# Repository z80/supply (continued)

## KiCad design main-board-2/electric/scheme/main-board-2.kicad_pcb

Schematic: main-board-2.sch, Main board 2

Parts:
C1, C6: 54u
C2, C4, C5, C14: 4u7
C3, C9, C10, C11, C12, C13, C15, C16: 100n
C7, C8: 18p
D1, D2: LED
D3, D4, D5, D6, D7, D8, D9, D10: 1n5819
K1: power-switch
K2: usb-power-switch
P1: batt
P3: trigger-btn
P4: CONN_3X2
P7: bootloader
P8: cross board conn
P9, P10: rst
P11: screw-1
P13: screw-2
P14: gpio-big
P15: gpio-small
P16: moto-1
P17: moto-2
Q1, Q3, Q4, Q9, Q10: IRLML2244
Q2, Q5, Q6, Q7, Q8: BC847
Q11: sot223
Q12: bc857
Q13: irlml2244
R1, R3, R6, R10, R22, R23, R26, R27: 1k
R2, R7, R9, R11, R12, R14, R18, R19, R20, R21, R24, R25, R28, R29, R30, R31: 30k
R4: 3k3
R5: 5k1
R8: 3k
R13: 50
R15, R16, R17: 10k
R32, R33: 22
R34: 1k5
R35: 100k
R36, R37, R38, R39: 0.1
R40, R42, R48, R49: 30k
R41, R43, R44, R45: 1k
R46, R47: 3
U1, U3: MY_LM317EMP; SOT-223
U2, U4: MY_LM317T; TO-220
U5: LM293
U6: L298
U7: MINI-USB-B
W1: sc-rpi-5v
W2: sc-addon-5v
W3: sc-addon-3.3
W4, W5, W10: TEST
W6: sc-sense-2
W7: sc-sense-1
W8: sc-moto-2
W9: sc-moto-1
X1: 8MHz
stm1: STM32F102C8T6

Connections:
/+5V: K1.2 (PM), K2.1, Q1.S, Q3.S, Q10.S, R9.2, R20.2, R30.1, W1.1, W2.1, W4.1
/addon-5V: P8.8, P8.9, Q3.D, W2.2
/addon-pwr-en: R22.1, R23.1, R24.2, stm1.26 (PB13/SPI2_SCK/USART3_CTS)
/addon-trigger: R17.2, stm1.19 (PB1/ADC_IN9/TIM3_CH4)
/addon-vdd: P8.6, P8.7, Q4.D, R15.1, R16.1, W3.2
/batt+: C1.1, C2.1, D3.2 (K), D5.2 (K), D7.2 (K), D9.2 (K), K1.3, P1.1, P8.10, P8.11, Q9.S, Q11.S, Q13.D, R28.1, R49.2, U1.3, U2.3, U3.3, U4.3, W5.1, W10.2
/cur-sense-1: R37.1, R39.1, U5.6 (_), U6.1 (current-sensing-A), W7.1
/cur-sense-2: R36.1, R38.1, U5.2 (_), U6.15 (current-sensing-B), W6.1
/d+: R33.1, stm1.33 (PA12/USART1_RTS/USBDP)
/d-: R32.1, stm1.32 (PA11/USART1_CTS/USBDM)
/gpio-1: P14.5, stm1.25 (PB12/SPI2_NSS/I2C2_SMBA/USART3_CTS)
/gpio-2: P14.11, stm1.18 (PB0/ADC_IN8/TIM3_CH3)
/gpio-3: P14.17, stm1.15 (PA5/SPI1_SCK/ADC_IN5)
/gpio-4: P14.23, stm1.13 (PA3/USART2_RX/ADC_IN3/TIM2_CH4)
/gpio-5: P14.6, stm1.27 (PB14/SPI2_MISO/USART3_RTS)
/gpio-6: P14.12, stm1.17 (PA7/SPI1_MOSI/ADC_IN7/TIM3_CH2)
/gpio-7: P14.18, stm1.16 (PA6/SPI1_MISO/ADC_IN6/TIM3_CH1)
/gpio-8: P14.24, stm1.14 (PA4/SPI1_NSS/ADC_IN4/USART2_CK)
/gpio-9: P15.1, stm1.12 (PA2/USART2_TX/ADC_IN2/TIM2_CH3)
/in-moto1: U6.5 (input-1), stm1.11 (PA1/USART2_RTS/ADC_IN1/TIM2_CH2)
/in-moto2: U6.7 (input-2), stm1.10 (PA0/WKUP/USART2_CTS/ADC_IN0/TIM2_CH1_ETR)
/in-moto3: U6.10 (input-3), stm1.3 (PC14/OSC32_IN)
/in-moto4: U6.12 (input-4), stm1.4 (PC15/OSC32_OUT)
/led1: R1.1, stm1.46 (PB9/TIM4_CH4^I2C1_SDA)
/led2: R3.1, stm1.45 (PB8/TIM4_CH3^I2C1_SCL)
/moto-en: R25.2, R26.1, R27.1, R44.1, R45.1, W8.1, W9.1, stm1.2 (PC13/TAMPER-RTC)
/moto-en-1: R45.2, U5.7, U6.6 (enable-A), W9.2
/moto-en-2: R44.2, U5.1, U6.11 (enable-B), W8.2
/out1: D9.1 (A), D10.2 (K), P16.1, U6.2 (output-1)
/out2: D7.1 (A), D8.2 (K), P16.2 (PM), U6.3 (output-2)
/out3: D5.1 (A), D6.2 (K), P17.1, U6.13 (output-3)
/out4: D3.1 (A), D4.2 (K), P17.2 (PM), U6.14 (output-4)
/pwrVs: C15.1, P14.3, P14.4, P14.9, P14.10, P14.15, P14.16, P14.21, P14.22, Q9.D, Q11.D, U6.4 (power_Vs), W5.2
/rpi-pwr-en: R10.1, R11.2, stm1.41 (PB5/I2C1_SMBA^TIM3_CH2/SPI1_MOSI)
/rx: P15.3, stm1.31 (PA10/USART1_RX)
/scl-int: P8.3, R16.2, stm1.21 (PB10/I2C2_SCL/USART3_TX^TIM2_CH3)
/scl-rpi: P4.5, stm1.42 (PB6/I2C1_SCL/TIM4_CH1^USART1_TX)
/sda-int: P8.2, R15.2, stm1.22 (PB11/I2C2_SDA/USART3_RX^TIM2_CH4)
/sda-rpi: P4.3, stm1.43 (PB7/I2C1_SDA/TIM4_CH3^USART1_RX)
/swd-clk: P15.4, stm1.37 (JTCK/SWCLK^PA14)
/swd-io: P15.6, stm1.34 (JTMS/SWDIO^PA13)
/trigger-button: P3.1, R2.1, stm1.29 (PA8/USART1_CK/MCO)
/tx: P15.5, stm1.30 (PA9/USART1_TX)
/usb-connected: R34.2, stm1.28 (PB15/SPI2_MOSI)
/usb-power: K2.2 (PM), U7.1 (VBus)
GND: C1.2, C2.2, C3.2, C4.2, C5.2, C6.2, C7.1, C8.1, C9.1, C10.2, C11.2, C12.2, C13.2, C14.2, C15.2, C16.2, D1.2 (K), D2.2 (K), D4.1 (A), D6.1 (A), D8.1 (A), D10.1 (A), P1.2 (PM), P3.2 (PM), P4.6, P8.4, P8.5, P10.1, P14.1, P14.2, P14.7, P14.8, P14.13, P14.14, P14.19, P14.20, P15.2, Q2.1 (E), Q5.1 (E), Q6.1 (E), Q8.1 (E), R4.2, R6.2, R11.1, R12.2, R24.1, R25.1, R29.2, R35.1, R36.2, R37.2, R38.2, R39.2, R41.2, R43.2, R48.1, U5.4 (V-), U6.8 (gnd), U6.tab (gnd), U7.0 (Shell), U7.5 (Gnd), W6.2, W7.2, stm1.8 (Vssa), stm1.20 (PB2/BOOT1), stm1.23 (Vss_1), stm1.35 (Vss_2), stm1.47 (Vss_3)
unnamed: P4.2, Q1.D, W1.2
unnamed: Q8.3 (C), R30.2, R31.1
unnamed: Q10.G, R31.2
unnamed: Q4.G, R19.2
unnamed: Q12.3 (C), Q13.G, R48.2, R49.1
unnamed: Q6.3 (C), R19.1, R21.1
unnamed: Q3.G, R18.2
unnamed: Q5.3 (C), R18.1, R20.1
unnamed: Q12.2 (B), Q13.S, R46.2, R47.2
unnamed: Q7.1 (E), R29.1
unnamed: Q7.2 (B), R26.2
unnamed: Q2.2 (B), R10.2
unnamed: Q2.3 (C), R7.1, R9.1
unnamed: Q7.3 (C), Q9.G, Q11.G, R28.2
unnamed: Q1.G, R7.2
unnamed: C16.1, Q10.D, U6.9 (logic_Vss), W4.2
unnamed: R40.2, R41.1, U5.3 (+)
unnamed: R42.2, R43.1, U5.5 (+)
unnamed: R32.2, U7.2 (D-)
unnamed: R35.2, U7.4 (Id)
unnamed: C9.2, P9.1, R14.2, stm1.7 (NRST)
unnamed: P7.2 (PM), R12.1, stm1.44 (BOOT0)
unnamed: Q5.2 (B), R22.2
unnamed: Q8.2 (B), R27.2
unnamed: R13.2, stm1.6 (PD1/OSC_OUT)
unnamed: C7.2, X1.2, stm1.5 (PD0/OSC_IN)
unnamed: C8.2, R13.1, X1.1
unnamed: D2.1 (A), R3.2
unnamed: D1.1 (A), R1.2
unnamed: Q6.2 (B), R23.2
unnamed: P8.1, R17.1
unnamed: K2.3, Q12.1 (E), R46.1, R47.1, W10.1
unnamed: C4.1, C6.1, K1.1, R8.2, U3.2, U3.4, U4.2
unnamed: R6.1, R8.1, U3.1, U4.1
unnamed: R4.1, R5.1, U1.1, U2.1
unnamed: R33.2, R34.1, U7.3 (D+)
VDD: C3.1, C5.1, C10.1, C11.1, C12.1, C13.1, C14.1, P7.1, Q4.S, R2.2, R5.2, R14.1, R21.2, R40.1, R42.1, U1.2, U1.4, U2.2, U5.8 (V+), W3.1, stm1.1 (Vbat), stm1.9 (Vdda), stm1.24 (Vdd_1), stm1.36 (Vdd_2), stm1.48 (Vdd_3)

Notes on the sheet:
Chassis motors control cheme.
Indicator LEDs for debugging.
Addon power.
No I2C pullups here as there are on raspberry-pi.
Battery connection socket.
Cross board communication socket. There is one at this board. But there should be two neighbour such sockets on all other boards to be able to stack them together.
Two unconnected pins for screws. The newest Raspberry Pi contains holes for M2.5 screws.
Pin 1 is for sort of synchronization if required.
Serial bootloader activation socket.
Vo*R2/(R1+R2) = 1.25 R1=5k1, R2=3k3 => Vo=3.181818...V.
Vo*R2/(R1+R2) = 1.25 R1=10k, R2=3k => Vo=5V.
This one is optional for high voltages >20V.
RPi power.
If jumper is here USB is a voltage output.
If jumper is here USB is a voltage input.
Install either TO-220 or SO-223
Either on/off circuit or shourt-circuit wire.
Again either a couple of short circuit wires or on/off circuit.
Current limiting to 400mA when USB is used for powering the board.
This one isn't actually needed for current limiting. But when powered from battery with voltage >12V GS voltage shouldn't be greater then 12V. This resistor makes it 1/2 of batt+ value.
Current sense 0.1Ohm x 2units are 0.05Ohm. At 2Amps it would be P=2^2*0.05 = 0.2W. 0.1W per one R unit. And it is <0.125W.
Here again either short circuit wires or circuits for current limiting.
This comparator has open collector output type. So it matters only when level goes low.
Short to gnd should be done using electrolytic capacitor hole.

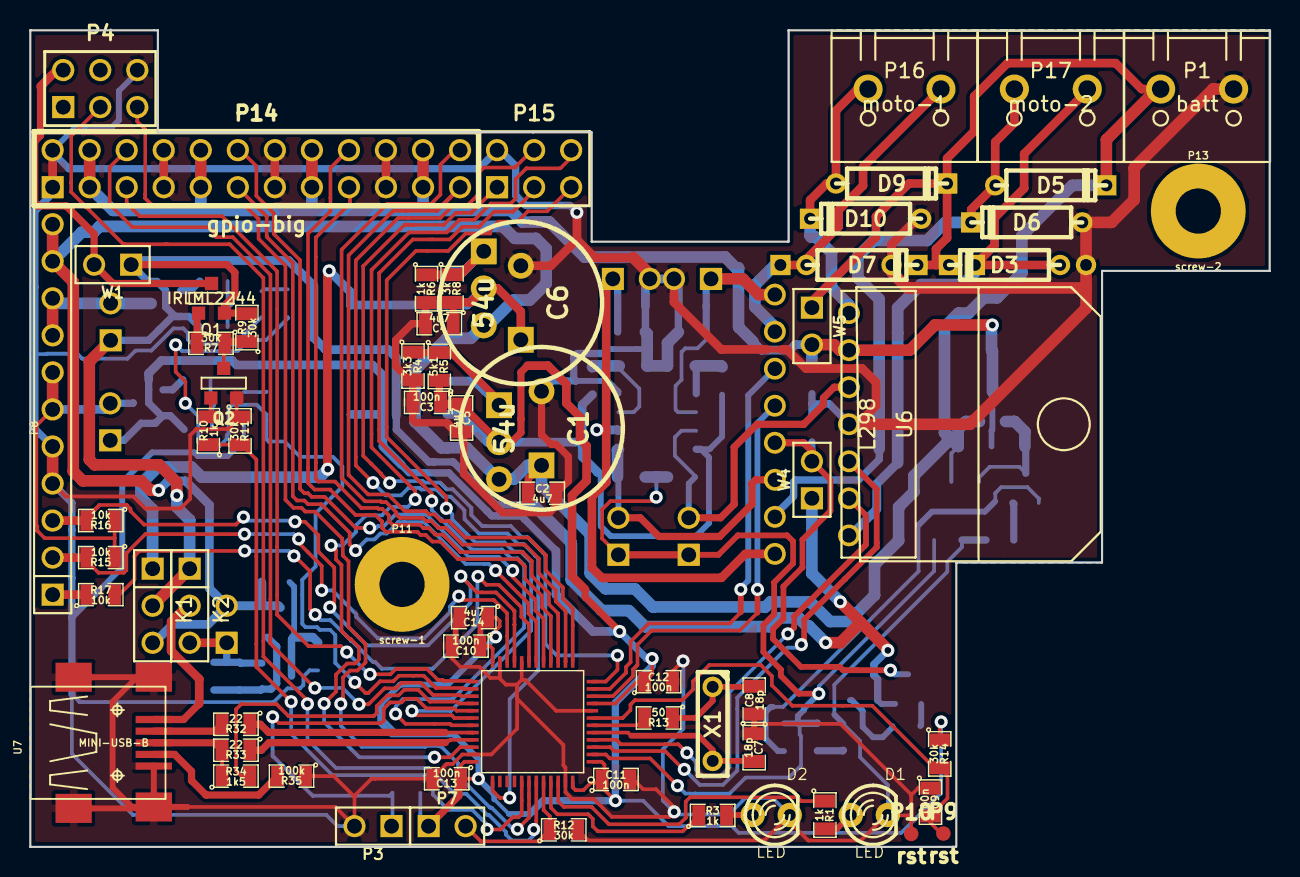
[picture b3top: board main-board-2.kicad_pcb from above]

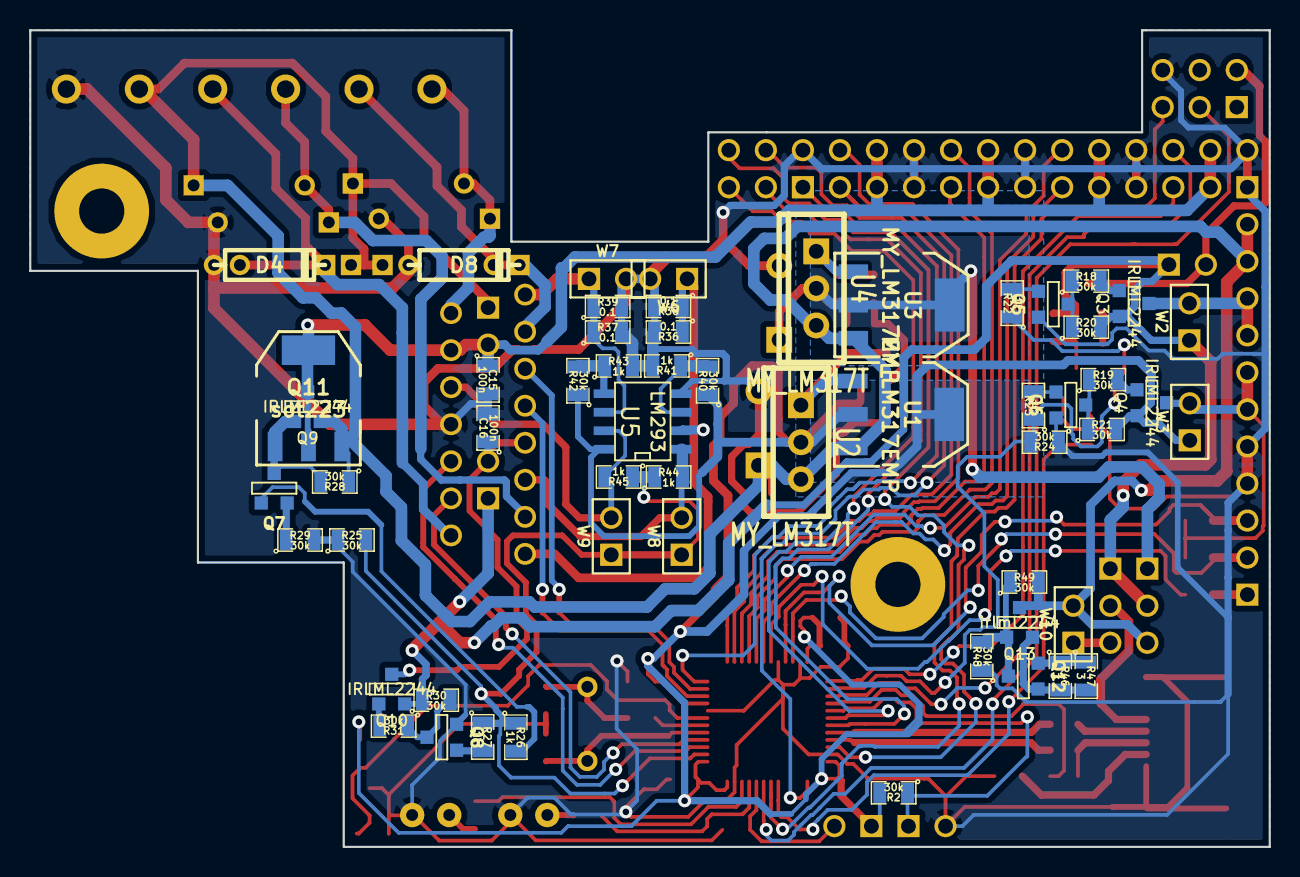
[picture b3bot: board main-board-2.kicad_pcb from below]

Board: 2 copper layers, 85.0 x 56.0 mm, 122 parts (56 on the bottom side), 83 nets.

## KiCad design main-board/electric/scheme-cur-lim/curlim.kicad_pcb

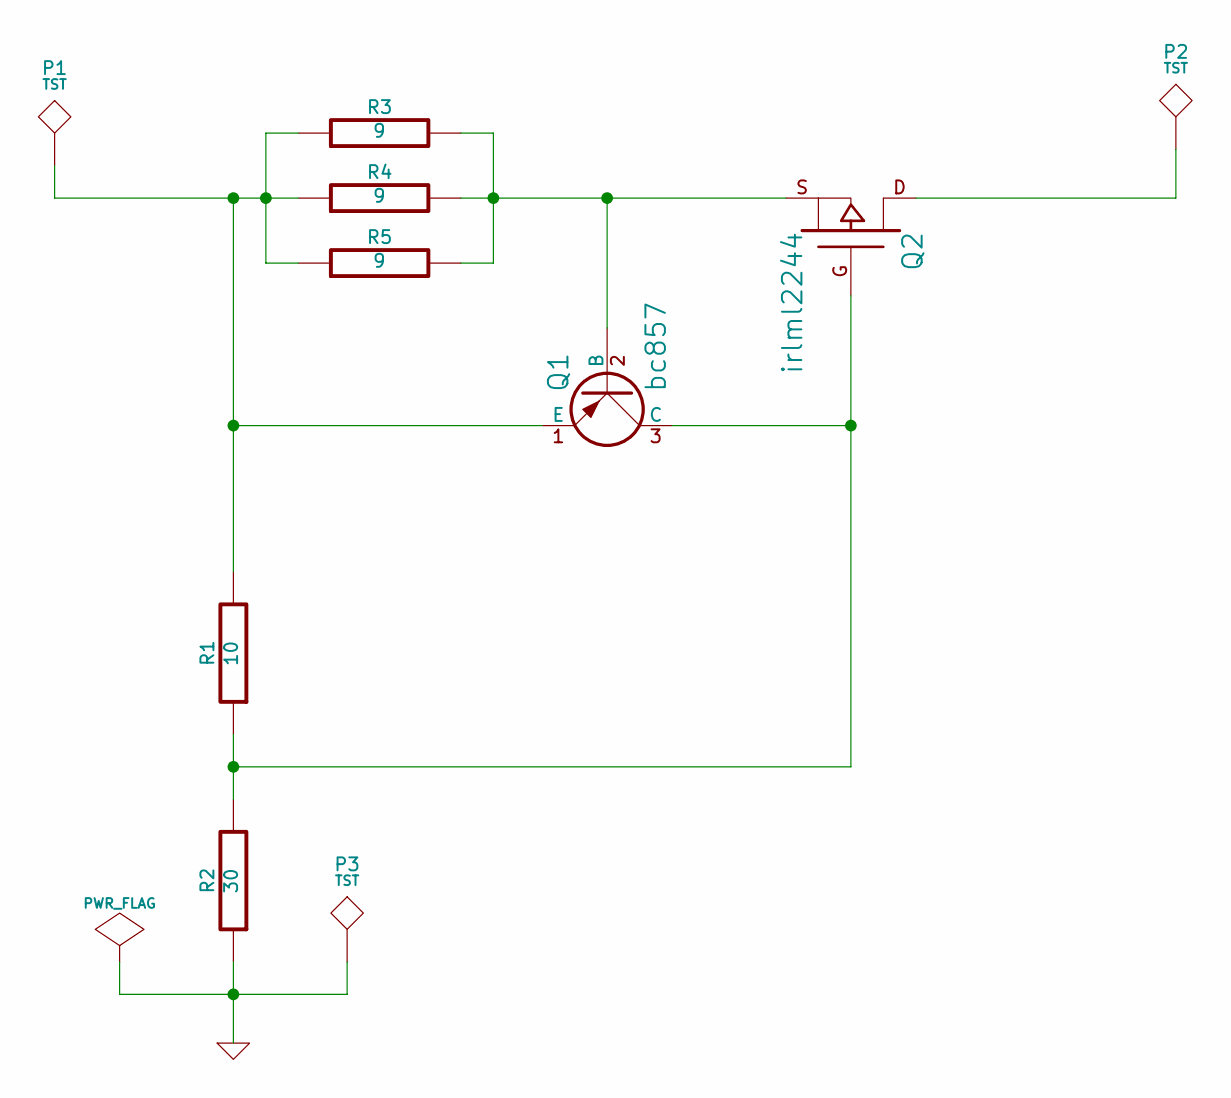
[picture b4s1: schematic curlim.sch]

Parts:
P1, P2, P3: TST
Q1: bc857
Q2: irlml2244
R1: 10
R2: 30
R3, R4, R5: 9

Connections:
GND: P3.1, R2.1
unnamed: Q1.3 (C), Q2.G, R1.1, R2.2
unnamed: P2.1, Q2.D
unnamed: Q1.2 (B), Q2.S, R3.2, R4.2, R5.2
unnamed: P1.1, Q1.1 (E), R1.2, R3.1, R4.1, R5.1

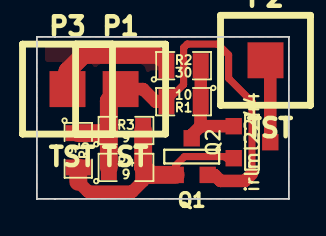
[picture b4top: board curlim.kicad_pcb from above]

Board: 2 copper layers, 14.0 x 9.0 mm, 10 parts (0 on the bottom side), 5 nets.

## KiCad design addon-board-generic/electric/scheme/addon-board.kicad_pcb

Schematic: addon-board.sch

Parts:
C1, C2, C3, C4, C5: 100n
C6: 10u
C7: 100n
C8: 10u
C9, C10: 18p
D1, D2: LED
K1, K2, K3, K4, K5, K6, K7, K8: CONN_3
P1, P2, P5, P6, P7, P8: TST
P3, P4: cross board conn
P9, P12, P13: CONN_4
P10: CONN_8
P11: CONN_10
Q1: NPN
Q2: IRLML2244
Q3, Q4: BC847
Q5, Q6: IRLML2244
R1, R2: 1k
R3, R4, R5, R6, R7, R8, R12, R13, R16, R17: 30k
R9: 1k
R10, R11: 30k
R14, R15: 500
R18, R19: 100
R20: 50
U1, U2: L293
U3: 74HC165
U4, U5: 74HC595_MY
X1: 8MHz
stm1: STM32F102C8T6

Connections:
+6V: Q5.S, Q6.S, R16.1, R17.1
/adc1: P10.1, stm1.11 (PA1/USART2_RTS/ADC_IN1/TIM2_CH2)
/adc2: P10.2, stm1.12 (PA2/USART2_TX/ADC_IN2/TIM2_CH3)
/adc3: P10.3, stm1.13 (PA3/USART2_RX/ADC_IN3/TIM2_CH4)
/adc4: P10.4, stm1.14 (PA4/SPI1_NSS/ADC_IN4/USART2_CK)
/adc5: P10.5, stm1.15 (PA5/SPI1_SCK/ADC_IN5)
/adc6: P10.6, stm1.16 (PA6/SPI1_MISO/ADC_IN6/TIM3_CH1)
/adc7: P10.7, stm1.17 (PA7/SPI1_MOSI/ADC_IN7/TIM3_CH2)
/addr0: P9.1, R8.2, stm1.27 (PB14/SPI2_MISO/USART3_RTS)
/addr1: P9.3, R7.2, stm1.28 (PB15/SPI2_MOSI)
/batt+: P3.8, P3.9, P4.8, P4.9, Q2.S
/buck-out-5v: P3.10, P3.11, P4.10, P4.11
/ds: U4.14, stm1.29 (PA8/USART1_CK/MCO)
/in0: P11.2, U3.11 (D0)
/in1: P11.3, U3.12 (D1)
/in2: P11.4, U3.13 (D2)
/in3: P11.5, U3.14 (D3)
/in4: P11.6, U3.3 (D4)
/in5: P11.7, U3.4 (D5)
/in6: P11.8, U3.5 (D6)
/in7: P11.9, U3.6 (D7)
/in-scl: U3.2 (CP), stm1.22 (PB11/I2C2_SDA/USART3_RX^TIM2_CH4)
/in-sda: U3.9 (Q7), stm1.21 (PB10/I2C2_SCL/USART3_TX^TIM2_CH3)
/iwakeup: P3.1, P4.1, R3.1
/led1: R1.1, U4.15
/led2: R2.1, U4.1
/moto1: U1.2 (in1), U4.4
/moto2: U1.9 (in2), U4.5
/moto3: U1.12 (in3), U4.6
/moto4: U1.19 (in4), U4.7
/moto5: U2.2 (in1), U5.15
/moto6: U2.9 (in2), U5.1
/moto7: U2.12 (in3), U5.2
/moto8: U2.19 (in4), U5.3
/moto-en1: R12.2, R14.1, U1.1 (en1), U1.11 (en2), U4.2
/moto-en2: R13.2, R15.1, U2.1 (en1), U2.11 (en2), U4.3
/mr: U4.10, U5.10, stm1.33 (PA12/USART1_RTS/USBDP)
/oe: U4.13, U5.13, stm1.30 (PA9/USART1_TX)
/out1: P12.3, U1.3 (out1)
/out2: P12.4, U1.8 (out2)
/out3: P12.1, U1.13 (out3)
/out4: P12.2, U1.18 (out4)
/out5: P13.3, U2.3 (out1)
/out6: P13.4, U2.8 (out2)
/out7: P13.1, U2.13 (out3)
/out8: P13.2, U2.18 (out4)
/scl-int: P3.3, P4.3, stm1.42 (PB6/I2C1_SCL/TIM4_CH1^USART1_TX)
/sda-int: P3.2, P4.2, stm1.43 (PB7/I2C1_SDA/TIM4_CH3^USART1_RX)
/servo1: K1.1, stm1.39 (JTDO^TIM2_CH2/PB3/TRACESWO/SPI1_SCKPB3)
/servo2: K2.1, stm1.40 (JNTRST^TIM3_CH1/PB4/SPI1_MISO)
/servo3: K3.1, stm1.41 (PB5/I2C1_SMBA^TIM3_CH2/SPI1_MOSI)
/servo4: K4.1, stm1.45 (PB8/TIM4_CH3^I2C1_SCL)
/servo5: K5.1, stm1.46 (PB9/TIM4_CH4^I2C1_SDA)
/servo6: K6.1, stm1.19 (PB1/ADC_IN9/TIM3_CH4)
/servo7: K7.1, stm1.18 (PB0/ADC_IN8/TIM3_CH3)
/servo8: K8.1, stm1.10 (PA0/WKUP/USART2_CTS/ADC_IN0/TIM2_CH1_ETR)
/servo-en: R9.1, U5.4
/servo-vdd+: C7.2, C8.2, K1.2 (PM), K2.2 (PM), K3.2 (PM), K4.2 (PM), K5.2 (PM), K6.2 (PM), K7.2 (PM), K8.2 (PM), Q2.D
/shcp: U4.11, U5.11, stm1.32 (PA11/USART1_CTS/USBDM)
/stcp: U4.12, U5.12, stm1.31 (PA10/USART1_RX)
/swd-clk: P5.1, stm1.37 (JTCK/SWCLK^PA14)
/swd-io: P6.1, stm1.34 (JTMS/SWDIO^PA13)
/wakeup: R3.2, stm1.3 (PC14/OSC32_IN)
/~in-load: U3.1 (~PL), stm1.26 (PB13/SPI2_SCK/USART3_CTS)
/~in-scl-en: U3.15 (~CE), stm1.25 (PB12/SPI2_NSS/I2C2_SMBA/USART3_CTS)
GND: C1.1, C2.2, C3.2, C4.2, C5.2, C6.2, C8.1, C9.1, C10.1, D1.2 (K), D2.2 (K), K1.3, K2.3, K3.3, K4.3, K5.3, K6.3, K7.3, K8.3, P3.4, P3.5, P4.4, P4.5, P7.1, P9.2, P9.4, P10.8, P11.1, P11.10, Q1.1 (E), Q3.1 (E), Q4.1 (E), R4.2, R5.2, R10.1, R11.2, R12.1, R13.1, U1.4 (gnd), U1.5 (gnd), U1.6 (gnd), U1.7 (gnd), U1.14 (gnd), U1.15 (gnd), U1.16 (gnd), U1.17 (gnd), U2.4 (gnd), U2.5 (gnd), U2.6 (gnd), U2.7 (gnd), U2.14 (gnd), U2.15 (gnd), U2.16 (gnd), U2.17 (gnd), U3.8 (GND), U4.8, U5.8, stm1.8 (Vssa), stm1.23 (Vss_1), stm1.35 (Vss_2), stm1.47 (Vss_3)
unnamed: Q3.3 (C), R16.2, R18.1
unnamed: Q5.D, U1.10 (vs), U1.20 (vss)
unnamed: Q5.G, R18.2
unnamed: Q3.2 (B), R14.2
unnamed: Q6.D, U2.10 (vs), U2.20 (vss)
unnamed: R4.1, stm1.44 (BOOT0)
unnamed: U4.9, U5.14
unnamed: C1.2, R6.2, stm1.7 (NRST)
unnamed: R5.1, stm1.20 (PB2/BOOT1)
unnamed: D2.1 (A), R2.2
unnamed: D1.1 (A), R1.2
unnamed: R20.2, stm1.6 (PD1/OSC_OUT)
unnamed: C10.2, R20.1, X1.1
unnamed: C9.2, X1.2, stm1.5 (PD0/OSC_IN)
unnamed: C7.1, Q1.3 (C), Q2.G, R11.1
unnamed: Q1.2 (B), R9.2, R10.2
unnamed: Q6.G, R19.2
unnamed: Q4.3 (C), R17.2, R19.1
unnamed: Q4.2 (B), R15.2
VDD: C2.1, C3.1, C4.1, C5.1, C6.1, P3.6, P3.7, P4.6, P4.7, R6.1, R7.1, R8.1, U3.10 (DS), U3.16 (VCC), U4.16, U5.16, stm1.1 (Vbat), stm1.9 (Vdda), stm1.24 (Vdd_1), stm1.36 (Vdd_2), stm1.48 (Vdd_3)

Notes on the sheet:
Chassis motors control cheme.
Indicator LEDs for debugging.
Programming socket is planned to be made of individual pads. And programming cable is supposed to be attached with crocodile clip.
Cross board communication socket. There is one at this board. But there should be two neighbour such sockets on all other boards to be able to stack them together.
Two unconnected pins for screws. The newest Raspberry Pi contains holes for M3 screws.
And four for screws at board corners.
Pin 1 is for waking up all other boards.

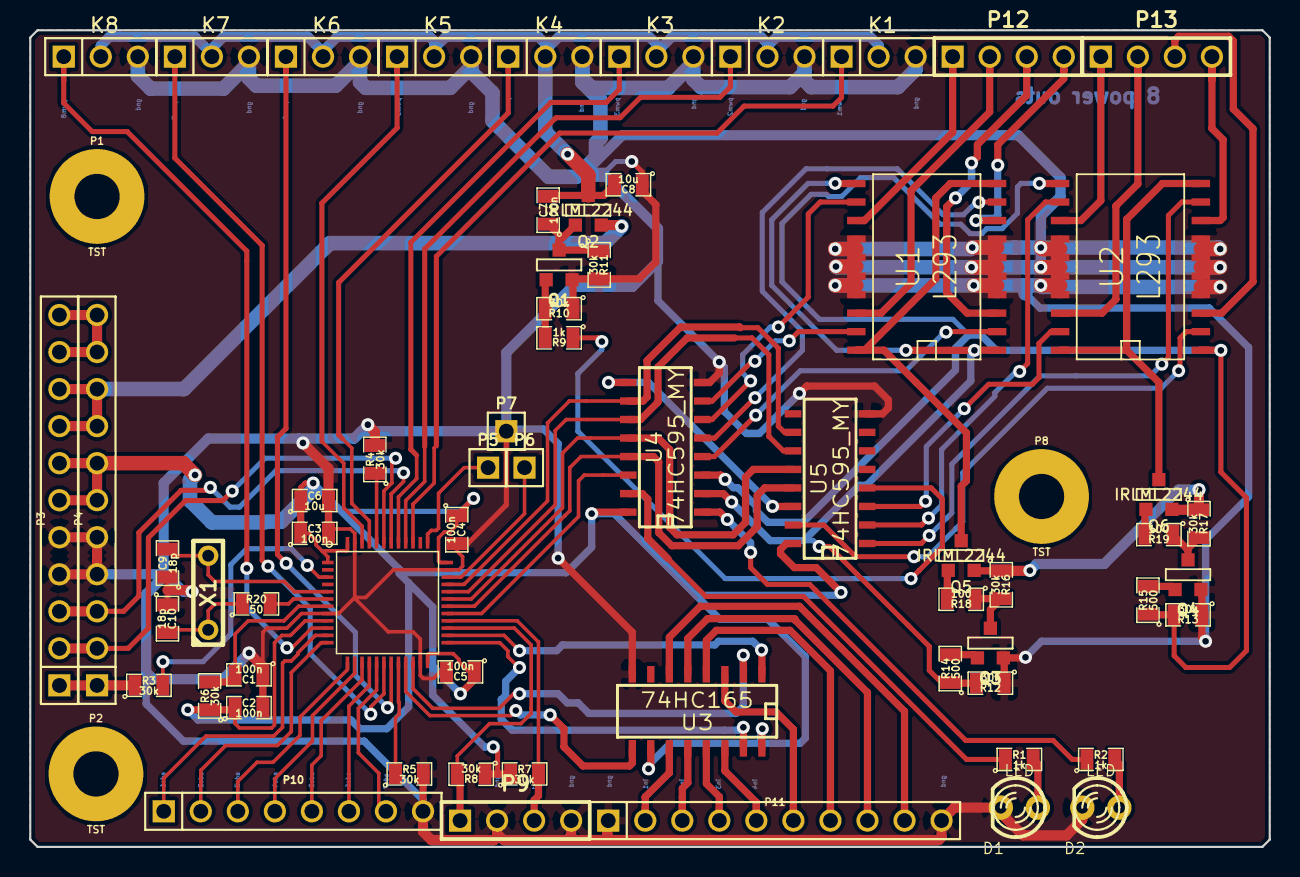
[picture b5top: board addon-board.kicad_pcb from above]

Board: 2 copper layers, 85.0 x 56.0 mm, 66 parts (0 on the bottom side), 86 nets.

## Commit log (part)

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2013-08-16 Started schematics.
2013-08-17 Board scheme development...
2013-08-19 More or less finished schema.
2013-08-20 Started placing components.
2013-08-21 Made footprints for components I didn't have footprints. And started placing components.
2013-08-23 Placing components...
2013-08-24 Placing elements.
2013-08-25 Places all but current measure circuit.
2013-08-26 Composed current measure circuit outside of the board.
2013-08-26 Routing.
2013-08-27 Routing...
2013-08-30 Routing and changing netlist to make routing more convenient.
2013-08-31 Routing is done. Added GND zones. I'm going to add text right in copper layer.
2013-08-31 Added socket labels.
2013-08-31 Added acelerometer (it's optional).
2013-08-31 .gitignore ignores _temp directory.
2013-08-31 Started extension board.
2013-09-02 Added shift registers to increase IO pins number.
2013-09-04 Placing components.
2013-09-06 Started routing.
2013-09-07 Finished routing. Holes for supports and cross board socket matches should be checked!
2013-09-07 Added more ground viases.
2013-09-09 Moved peripherial sockets closer to outer board edge.
2013-09-10 Started composing BOT for purchasing.
2013-09-10 Raplaced power mosfets with sot23 transistors because of their max current and very low resistance.
2013-09-10 For boost and buck circuits made optional sot23/sot223 transistor packages.
2013-09-11 DFU firmware. Pins adjusted for supply board.
2013-09-11 DFU software from related repository.
2013-09-11 Firmware is copied from DFU repository.
2013-09-11 Editing board.h to match current board.
2013-09-12 Splitted project into two with common code.
2013-09-13 Listed erros detected!!!
2013-09-14 Started converter implementation.
2013-09-14 Voltage converter processing.
2013-09-14 Updated ToDo list.
2013-09-15 Implemented LED and Motor control files.
2013-09-15 Fixing errors.
2013-09-16 Minimized thread switch time. Made threads cooperative.
2013-09-16 Recompiled firmware.
2013-09-17 Added one more addition.
2013-09-18 Changing pawn_pinding. Going to add RTC support.
2013-09-19 The very first in my life web design attempt.
2013-09-20 Rebuilt DFU in debug mode.
2013-09-20 Rebuilt DFU in size optimization mode.
2013-09-22 In such a way it works. But when I insert chThdSleepMilliseconds() function it hangs up at the location of the very first entry of that function.
2013-09-22 LED and Light work.
2013-09-22 Fixed ADC signal indices. Buck works.
2013-09-23 Filling Pawn binding functions.
2013-09-23 I was filling functionality.
2013-09-23 Project compiles with I2C support inserted.
2013-09-23 Filling Pawn functions.
2013-09-23 Fixed serial_ctrl.c.
2013-09-24 Adjusted TODO list.
2013-09-24 Adjusted DFU firmware. Now the idea is to start regular firmware and if trigger is pulled down invoke DFU firmware from the very end of FLASH memory.
2013-09-24 Adjusted trigger and dfu functionality. Added trigger querying function to Pawn.
2013-09-24 Rebuild under Linux.
2013-09-25 Started software. Added Pawn compiler.
2013-09-25 Preapred test for flashing Pawn scripts checking.
2013-09-25 Binary files to build in Windows.
2013-09-25 DFU library compiles under Windows.
2013-09-25 Removed unnecessary warning.
2013-09-25 .gitignore is modified to ignore unnecessary files.
2013-09-25 Fixed USB connect/disconnect pin.
2013-09-25 Investigating the root of a problem why USB device presents but nothing coul'd be written here. At this line it works.
2013-09-25 Up to this moment USB IO works through GtkTerm utility.
2013-09-26 Added pawnStart and pawnStop functions to control library.
2013-09-26 Making setIo(), io() functions in the library.
2013-09-26 Moto chip test works.
2013-09-28 Changed io commands. Changed command names.
2013-09-28 Decreased command lengths. Implemented reading back results through USB.
2013-09-29 Changed DFU check and set Pawn start page to be 38.
2013-09-29 Uncommented DFU check and checged trigger polarity in DFU check function.
2013-09-29 Rearranged items in pawn project.
2013-09-29 Now DFU check seems to work.
2013-09-29 Fixed setIo() and io() functions in usbctrl library. These functions work properly. But io() worsk very slowly(!!!).
2013-09-29 Trying to make DFU work.
2013-09-29 Fixed DFU USB on/off functionality.
2013-09-29 Shifted DFU location address.
2013-09-29 Fixed trigger position.
2013-09-29 Rebuilt firmware.
2013-09-29 Debugging DFU.
2013-09-30 In DFU mode start there was wrong jump address. After fixing DFU firmware starts properly. At list it is shown in "lsusb" output.
2013-09-30 Another DFU software. This time it is with bin to dfu converter.
2013-09-30 Changed DFU write address.
2013-09-30 Changed all 2048 mentions to 1024.
2013-09-30 I2C test failed. Probably it is because accelerometer is not soldered well.
2013-09-30 Boost test disclosed imperfectness of boost algorithm. Had to decrease boost gain to make it work more precisely.
2013-09-30 Fixed temperature measure. Implemented temperature measure test.
2013-10-01 Heap/Stack size shouldn't be set more then they are. Acceleroneter responds but returns constant value "149" from all
2013-10-01 Increased IO size up to 32 and Pawn memory up to 10240.
2013-10-01 Debugging: changing Pawn thread stack size and virtual machine memory size.
2013-10-01 Fixed I2C IO function.
2013-10-03 Started addon-board firmware design.
2013-10-04 Filling functionality.
2013-10-04 Just before trying to compile for the first time.
2013-10-04 Made project compilable. Commented out all but testing LEDs.
2013-10-05 There is just 10k of RAM.
2013-10-05 Found schematic problem: +6V and batt+ circuits are not connected.
2013-10-05 Led and Moto controls work properly.
2013-10-05 PWM doesn't work at all. Any PWM enable channel causes failure.
2013-10-05 If anything related to PWM is uncommented CPU jumps to unhandled exception.
2013-10-05 Standard PWM HAL test works.
2013-10-05 Removed unused stuff from mcucfg.h and it still works.
2013-10-05 Works in native firmware.
2013-10-05 PWM initialization works.
2013-10-05 It seems ADC works as well. Default value is about 340.
2013-10-05 Sleep and wakeup controls initialize without crashes.
2013-10-05 I2C initialization passed.
2013-10-05 Inverted address meaning.
2013-10-05 Well, it looks like it runs.
2013-10-06 Started addon Pawn header.
2013-10-06 LEDs test for addon board works. It meand I2C communication works as well.
2013-10-07 Implemented voltage, temperature and current conversion formulas.
2013-10-07 Formulas calculation in Maxima.
2013-10-07 Maximum current test. It seems it is failed. Current is 4 times greater then expected and a bit less then V/R. Current set was 100mA, obtained - 340mA, V/R = 2000/3 = 666.7mA.
2013-10-07 Fixed RTC functionality. Now it should match one from firmware.
2013-10-08 Turned size optimization on for addon board firmware.
2013-10-08 Circle LEDs. And it works.
2013-10-08 Decreased ADC period.
2013-10-08 Added simple GUI made in Python.
2013-10-08 Worked with install directories structure. Added prototype for python USB module.
2013-10-08 Renamings and added I2C module.
2013-10-09 Fixed error for Windows.
2013-10-09 Python modules compile but don't have proper names.
2013-10-09 Python binary modules are opened by Python, rearranged includes and tests for Pawn.
2013-10-11 Fixed a couple of bugs in GUI.
2013-10-11 Started documenting features.
2013-10-13 Renamed script api file.
2013-10-13 Editing docs.
2013-10-14 Filled funcs related to PWM.
2013-10-14 Fixed addSetPwm() function.
2013-10-15 Scripts proceeds if trigger button is pressed.
2013-10-15 Servo control works. Period 20ms, duty cycle from 1ms to 2ms.
2013-10-15 Works with Raspberry Pi powering.
2013-10-15 Added nice comments to pi_buck_test.p file.
2013-10-15 3 seconds Pawn start delay.
2013-10-15 Description added.
2013-10-16 Renamed Pawn scripts directory. Added directory for python scripts and modules.
2013-10-16 Reflash of "bad" script file works!!!
2013-10-16 Fixed python test script.
2013-10-16 Improved servo from python control test.
2013-10-16 Execution string in python test script.
2013-10-21 Rotating camera example. Sources for Python.
2013-10-21 Forgotten to add i2c test.
2013-10-22 Seems ADC and input functions work. For ADC function it was an error in result return. It was written in worng place. Now it is fixed.
2013-10-22 Input and ADC test works. Or at least it looks so.
2013-10-23 EEPROM interaction script.
2013-10-23 EEPROM Python script.
2013-10-23 Saved data for two sequential pages count.
2013-10-25 Board interaction description file.
2013-10-25 Attempt to make compillable for windows.
2013-10-25 Windows driver.
2013-10-25 Compiles for windows with dynamic boost-python library! With statis still doesn't work :(
2013-10-25 Adjusted HTML documentation and size of main GUI window.
2013-10-25 Modified todo list.
2013-10-26 Scripts for serious test.
2013-10-27 Added Light on/off function to firmware.
2013-10-27 Inserted the same to robot script.
2013-10-27 Made DFU size #define constant.
2013-10-27 Reduce robot.p script functionality.
2013-10-27 Script for testing works through USB.
2013-10-28 editing...
2013-10-28 Todo list extended. Robot script is adjusted.
2013-10-29 Appended todo list.
2013-10-29 Separate current limiting circuit.
2013-10-29 ToDo is extended with one more point.
2013-10-30 ToDo and plan are updated.
2013-10-30 First raw plan.
2013-10-30 Corrected the plan.
2013-11-08 Moto demonstration.
2013-11-12 For Windows made using libusb0.
2013-11-12 Added some fixes. Should be checked...
2013-11-13 Flashing and Io works for Windows.
2013-11-13 Increased IO speed.
2013-11-15 SCiTE configuration files in progress...
2013-11-16 Commented about upper voltage dividing resistor.
2013-11-16 Added to todo list.
2013-11-16 Modified "build" and "go" commands.
2013-11-17 Bootloader manual.
2013-11-20 Scratch communication.
2013-11-20 Extended TODO list.
2013-11-21 Simple Scratch interaction module.
2013-11-25 Included SciTE in Windows distribution.
2013-11-26 Adjusted for Linux.
2013-11-26 Experimented with scratch. It sends var values normally. But it doesn't get var values from Python.
2013-11-26 Prepared for scratch demo.
2013-11-27 Updates ToDo list.
2013-11-28 OpenCV play around...
2013-12-01 Chessboard failed attempts...
2013-12-06 Made scheme for main-board-2.
2013-12-07 Optimizing board...
2013-12-07 Assigned components to footprints.
2013-12-08 Placing elements...
2013-12-08 Removed unused screw holes.
2013-12-09 Routing. Made servo power switchable.
2013-12-10 Routing. It turnes out it is very nontrivial to route with horizontal TO-220. I'm going to change to vertical TO-220.
2013-12-10 Changed packages to vertical ones.
2013-12-11 Just one more circuit Vdd to addon socket last.
2013-12-11 Just connected all unconnected circuits.
2013-12-11 Added comments.
2013-12-12 Places zones and made thermal take zones under regulators.
2013-12-12 Displaced TO-220 regulators.
2013-12-12 Forgot to save scheme.
2013-12-12 Changed paintings.
2013-12-12 Made Vdd wire to MCU a bit wider.
2013-12-12 Firmware folder is copied to main-board-2 folder.
2013-12-12 Adjusting DFU firmware.
2013-12-12 Reverted user button processing in DFU firmware.
2013-12-12 Application address is set to be 10k, e.i. 2800.
2013-12-12 Compiled DFU.
2013-12-12 Adjusting firmware for a new design...
2013-12-12 Adjusted pads and ports to the new board.
2013-12-13 Making GPIO module.
2013-12-13 Implemented PWM using Timer callback.
2013-12-13 Editing gpio service routines...
2013-12-14 Changed contacts locations on power source selection sockets.
2013-12-14 Implemented several new functions.
2013-12-14 Adjusted Pawn settings.
2013-12-14 Made Pawn header and it's installation.
2013-12-15 Exported gerber files.
2013-12-15 Made power switching automatic for both pwm and moto.
2013-12-21 Placed elements on addon board with gpio.
2013-12-23 Routed. Making silcography.
2013-12-23 Made drawing with connections scheme.
2013-12-23 Added small accelerometer module.
2014-01-11 Added addon board description.
2014-02-06 Started etching script.
2014-02-10 Etching GUI prototyping.
2014-02-11 Found unnecessary conversion from ADC to temperature.
